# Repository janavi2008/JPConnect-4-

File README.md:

# JPConnect(4)
a 2-player connect 4 game hardware project from scratch with a minimalist design. Connect 4 is a fun boardgame that ive played throughout my childhood, and i thought it'd be an interesting challenge to replicate it on a pcb. Since its portable, its a great way to pass the time on trips, or anywhere else.

it operates on a 6x7 (vertical) grid, with one player getting red coins and the other yellow. the players take turns placing a coin, with the objective of getting 4 of their colour in a row (horizontal, vertical and diagonal count)

besides the connect for game, this project has tons of scope for upgrading in the future, without hardware changes - just changing the code can allow a variety of games to be added - X and 0s, snake, pong, etc.

# Design
Uses an arduino nano, 2 MAX7219 driver chips, 2 7x7 led matrices of different colours, one for each player, push buttons for control, some leds to indicate turns and a buzzer for winning sounds. the components are smd for a cleaner look and to save space, except for the nano.

The nano(microcontroller) acts as the brain, taking data from the buttons(input devices), processing it(deciding what to do next), and then sending insstructions to the MAX7219 chips(display drivers), and the buzzer(output device). the MAX7219s are required as we have 98 leds in the matrices, and the nano has only 22 input/output pins. using the MAX7219s allows us to operate all 98 leds using only 3 pins - clock, load, and data in.

im currently planning on using usb as the primary power source, but since the goal is to make it portable, ill be adding a way to power it using batteries once its ready.

# GamePlay
its played like a regular connect 4 game, the actual game is a 6x7 grid and there is one row for the "cursor", which blinks over the selected column. there are three push buttons on each side of the grid, one set for each player (left, right, and confirm). the entire game display flips to face the player whose turn it is, so its easy to understand. winning is auto detected, as well as draw/filled board, and the game resets.

# Bill of Materials

  Part                                  | Quantity | Supplier | Price |
|---------------------------------------|----------|----------|-------|
| PCB                                   | 1        | JLCPCB   | $9.20 |
| Arduino Nano                          | 1        | Robu.in  | $2.50 |
| MAX7219 IC chip (or MAX7221)          | 2        | Robu.in  | $1    |
| female header pins                    | 30       | Robu.in  | $0.5  |
| 1206 smd LED (red)                    | 50       | Robu.in  | $0.5  |
| 1206 smd LED (yellow)                 | 50       | Robu.in  | $0.5  |
| 0805 smd 1k resistor                  | 2        | Robu.in  | $0.01 |
| 0805 smd 20k resistor                 | 2        | Robu.in  | $0.01 |
| 0805 smd 10uF capacitor               | 2        | Robu.in  | $0.01 |
| 0805 smd 100nF capacitor              | 2        | Robu.in  | $0.01 |
| 12mm through hole push button         | 6        | Robu.in  | $0.8  |
| 8x10 smd 470uF electrolytic capacitor | 1        | Robu.in  | $0.5  |
| 12x9.5mm active buzzer                | 1        | Robu.in  | $0.4  |

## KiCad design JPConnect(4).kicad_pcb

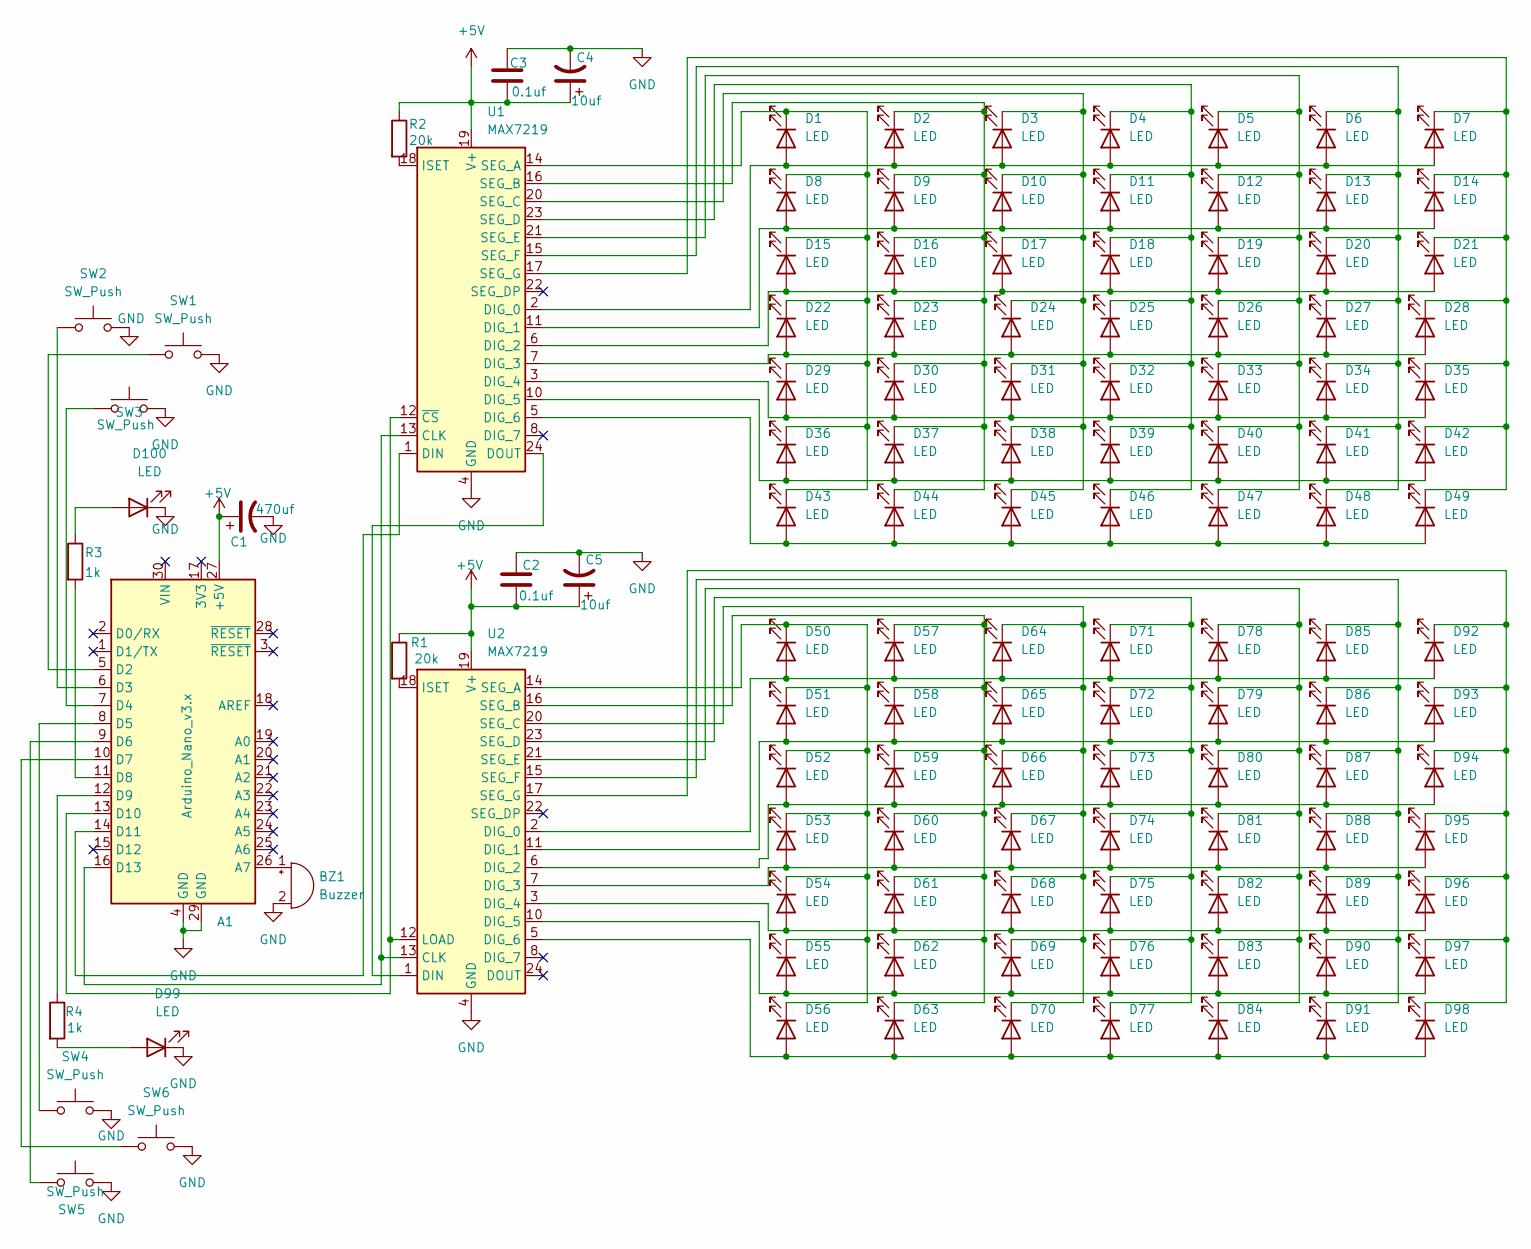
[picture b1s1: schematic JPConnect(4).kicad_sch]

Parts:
A1: Arduino_Nano_v3.x; Arduino_Nano
BZ1: Buzzer; Buzzer_12x9.5RM7.6
C1: 470uf; CP_Elec_8x10
C2, C3: 0.1uf; C_0805_2012Metric_Pad1.18x1.45mm_HandSolder
C4, C5: 10uf; C_0805_2012Metric_Pad1.18x1.45mm_HandSolder
D1, D2, D3, D4, D5, D6, D7, D8, D9, D10, D11, D12, D13, D14, D15, D16, D17, D18, D19, D20, D21, D22, D23, D24, D25, D26, D27, D28, D29, D30, D31, D32, D33, D34, D35, D36, D37, D38, D39, D40, D41, D42, D43, D44, D45, D46, D47, D48, D49, D50, D51, D52, D53, D54, D55, D56, D57, D58, D59, D60, D61, D62, D63, D64, D65, D66, D67, D68, D69, D70, D71, D72, D73, D74, D75, D76, D77, D78, D79, D80, D81, D82, D83, D84, D85, D86, D87, D88, D89, D90, D91, D92, D93, D94, D95, D96, D97, D98, D99, D100: LED; LED_1206_3216Metric_Pad1.42x1.75mm_HandSolder
R1, R2: 20k; R_0805_2012Metric_Pad1.20x1.40mm_HandSolder
R3, R4: 1k; R_0805_2012Metric_Pad1.20x1.40mm_HandSolder
SW1, SW2, SW3, SW4, SW5, SW6: SW_Push; SW_PUSH-12mm
U1, U2: MAX7219; SOIC-24W_7.5x15.4mm_P1.27mm

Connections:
+5V: A1.27 (+5V), C1.1, C2.2, C3.2, C4.1, C5.1, R1.1, R2.1, U1.19 (V+), U2.19 (V+)
GND: A1.4 (GND), A1.29 (GND), BZ1.2 (-), C1.2, C2.1, C3.1, C4.2, C5.2, D99.1 (K), D100.1 (K), SW1.2, SW2.2, SW3.2, SW4.2, SW5.2, SW6.2, U1.4 (GND), U1.9 (GND), U2.4 (GND), U2.9 (GND)
unnamed: A1.26 (A7), BZ1.1 (+)
unnamed: A1.5 (D2), SW1.1
unnamed: A1.6 (D3), SW2.1
unnamed: A1.7 (D4), SW3.1
unnamed: A1.8 (D5), SW4.1
unnamed: A1.9 (D6), SW5.1
unnamed: A1.10 (D7), SW6.1
unnamed: A1.11 (D8), R3.2
unnamed: A1.12 (D9), R4.1
unnamed: A1.13 (D10), U1.12 (~CS), U2.12 (LOAD)
unnamed: A1.14 (D11), U1.1 (DIN)
unnamed: A1.16 (D13), U1.13 (CLK), U2.13 (CLK)
unnamed: D1.2 (A), D2.2 (A), D3.2 (A), D4.2 (A), D5.2 (A), D6.2 (A), D7.2 (A), U1.2 (DIG_0)
unnamed: D1.1 (K), D8.1 (K), D15.1 (K), D22.1 (K), D29.1 (K), D36.1 (K), D43.1 (K), U1.14 (SEG_A)
unnamed: D8.2 (A), D9.2 (A), D10.2 (A), D11.2 (A), D12.2 (A), D13.2 (A), D14.2 (A), U1.11 (DIG_1)
unnamed: D3.1 (K), D10.1 (K), D17.1 (K), D24.1 (K), D31.1 (K), D38.1 (K), D45.1 (K), U1.20 (SEG_C)
unnamed: D4.1 (K), D11.1 (K), D18.1 (K), D25.1 (K), D32.1 (K), D39.1 (K), D46.1 (K), U1.23 (SEG_D)
unnamed: D5.1 (K), D12.1 (K), D19.1 (K), D26.1 (K), D33.1 (K), D40.1 (K), D47.1 (K), U1.21 (SEG_E)
unnamed: D6.1 (K), D13.1 (K), D20.1 (K), D27.1 (K), D34.1 (K), D41.1 (K), D48.1 (K), U1.15 (SEG_F)
unnamed: D7.1 (K), D14.1 (K), D21.1 (K), D28.1 (K), D35.1 (K), D42.1 (K), D49.1 (K), U1.17 (SEG_G)
unnamed: D15.2 (A), D16.2 (A), D17.2 (A), D18.2 (A), D19.2 (A), D20.2 (A), D21.2 (A), U1.6 (DIG_2)
unnamed: D2.1 (K), D9.1 (K), D16.1 (K), D23.1 (K), D30.1 (K), D37.1 (K), D44.1 (K), U1.16 (SEG_B)
unnamed: D22.2 (A), D23.2 (A), D24.2 (A), D25.2 (A), D26.2 (A), D27.2 (A), D28.2 (A), U1.7 (DIG_3)
unnamed: D29.2 (A), D30.2 (A), D31.2 (A), D32.2 (A), D33.2 (A), D34.2 (A), D35.2 (A), U1.3 (DIG_4)
unnamed: D36.2 (A), D37.2 (A), D38.2 (A), D39.2 (A), D40.2 (A), D41.2 (A), D42.2 (A), U1.10 (DIG_5)
unnamed: D43.2 (A), D44.2 (A), D45.2 (A), D46.2 (A), D47.2 (A), D48.2 (A), D49.2 (A), U1.5 (DIG_6)
unnamed: D50.2 (A), D57.2 (A), D64.2 (A), D71.2 (A), D78.2 (A), D85.2 (A), D92.2 (A), U2.2 (DIG_0)
unnamed: D50.1 (K), D51.1 (K), D52.1 (K), D53.1 (K), D54.1 (K), D55.1 (K), D56.1 (K), U2.14 (SEG_A)
unnamed: D51.2 (A), D58.2 (A), D65.2 (A), D72.2 (A), D79.2 (A), D86.2 (A), D93.2 (A), U2.11 (DIG_1)
unnamed: D52.2 (A), D59.2 (A), D66.2 (A), D73.2 (A), D80.2 (A), D87.2 (A), D94.2 (A), U2.6 (DIG_2)
unnamed: D53.2 (A), D60.2 (A), D67.2 (A), D74.2 (A), D81.2 (A), D88.2 (A), D95.2 (A), U2.7 (DIG_3)
unnamed: D54.2 (A), D61.2 (A), D68.2 (A), D75.2 (A), D82.2 (A), D89.2 (A), D96.2 (A), U2.3 (DIG_4)
unnamed: D55.2 (A), D62.2 (A), D69.2 (A), D76.2 (A), D83.2 (A), D90.2 (A), D97.2 (A), U2.10 (DIG_5)
unnamed: D56.2 (A), D63.2 (A), D70.2 (A), D77.2 (A), D84.2 (A), D91.2 (A), D98.2 (A), U2.5 (DIG_6)
unnamed: D57.1 (K), D58.1 (K), D59.1 (K), D60.1 (K), D61.1 (K), D62.1 (K), D63.1 (K), U2.16 (SEG_B)
unnamed: D64.1 (K), D65.1 (K), D66.1 (K), D67.1 (K), D68.1 (K), D69.1 (K), D70.1 (K), U2.20 (SEG_C)
unnamed: D71.1 (K), D72.1 (K), D73.1 (K), D74.1 (K), D75.1 (K), D76.1 (K), D77.1 (K), U2.23 (SEG_D)
unnamed: D78.1 (K), D79.1 (K), D80.1 (K), D81.1 (K), D82.1 (K), D83.1 (K), D84.1 (K), U2.21 (SEG_E)
unnamed: D85.1 (K), D86.1 (K), D87.1 (K), D88.1 (K), D89.1 (K), D90.1 (K), D91.1 (K), U2.15 (SEG_F)
unnamed: D92.1 (K), D93.1 (K), D94.1 (K), D95.1 (K), D96.1 (K), D97.1 (K), D98.1 (K), U2.17 (SEG_G)
unnamed: D99.2 (A), R4.2
unnamed: D100.2 (A), R3.1
unnamed: U1.24 (DOUT), U2.1 (DIN)
unnamed: R2.2, U1.18 (ISET)
unnamed: R1.2, U2.18 (ISET)

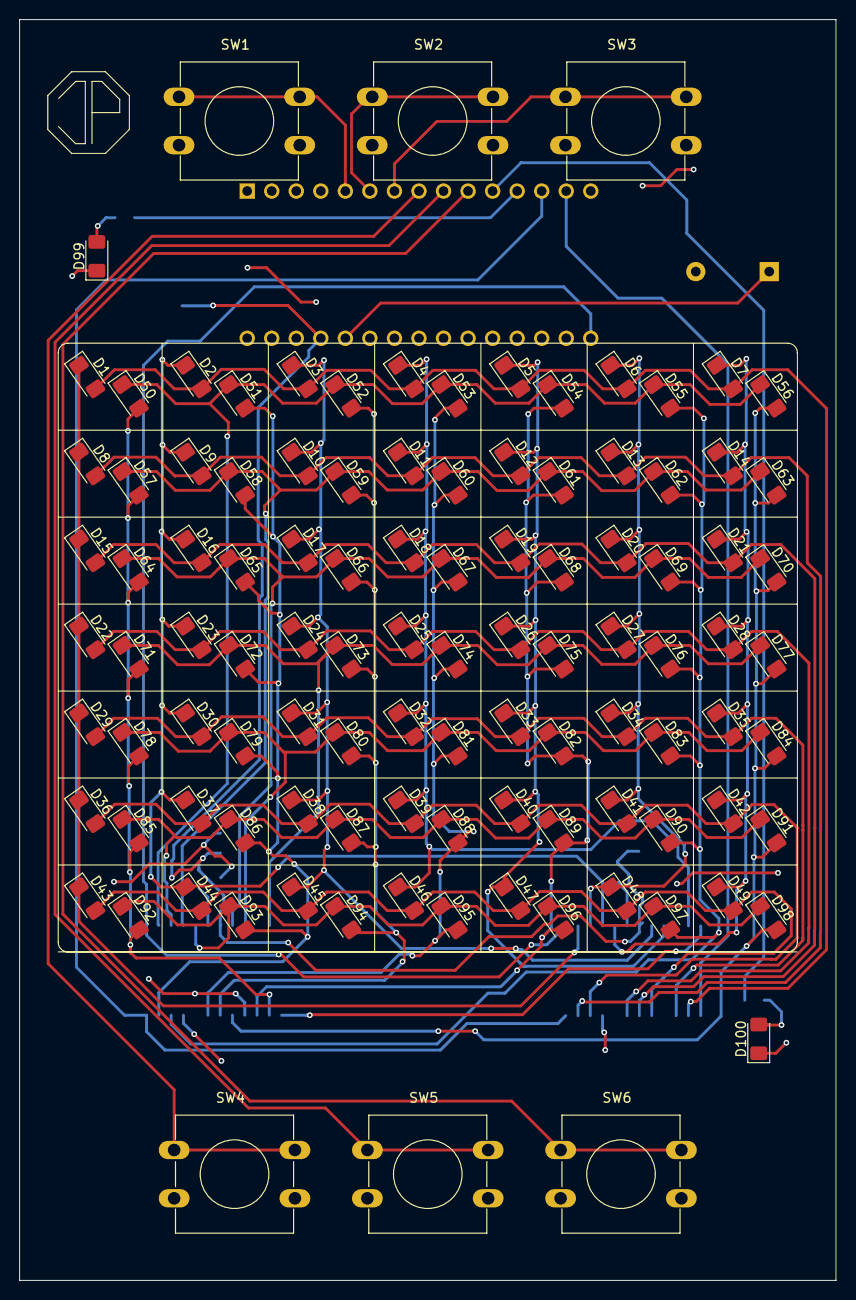
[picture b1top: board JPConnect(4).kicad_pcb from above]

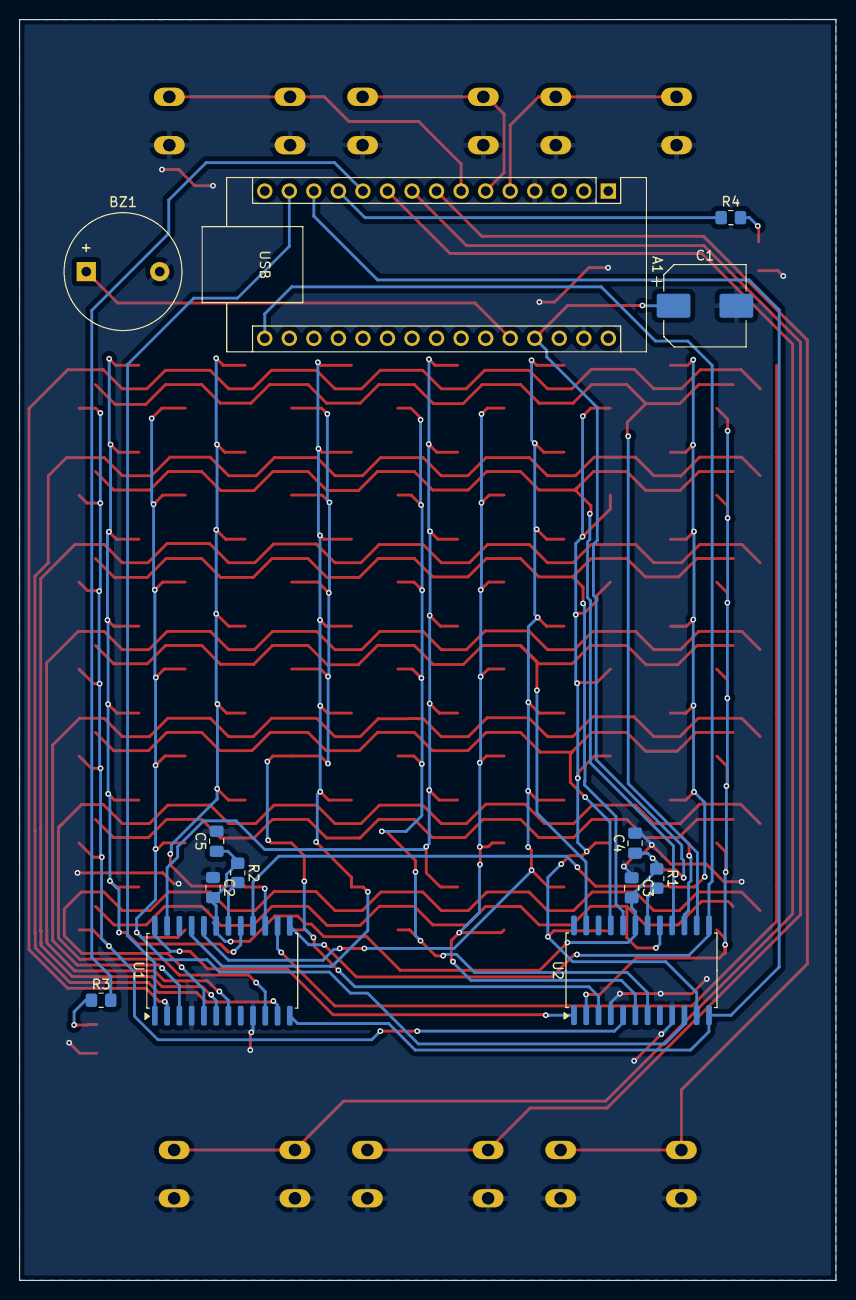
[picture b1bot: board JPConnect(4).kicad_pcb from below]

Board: 2 copper layers, 84.5 x 130.5 mm, 119 parts (13 on the bottom side), 47 nets.
